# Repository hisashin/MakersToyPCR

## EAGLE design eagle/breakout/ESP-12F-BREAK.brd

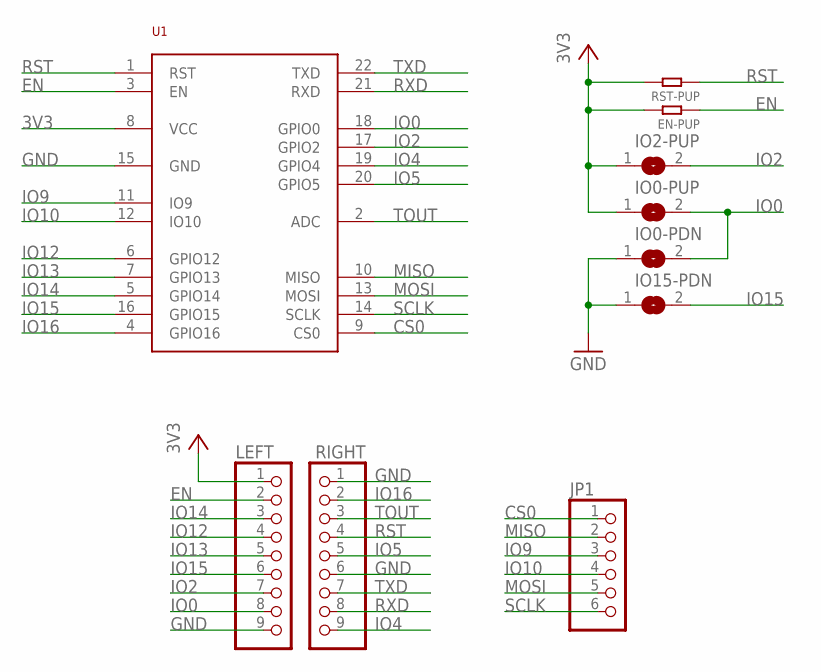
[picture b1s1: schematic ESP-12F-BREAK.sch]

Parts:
EN-PUP: 10K; R0805
IO0-PDN, IO0-PUP, IO2-PUP, IO15-PDN: SJ
JP1: PINHD-1X6; 1X06
LEFT: PINHD-1X9; 1X09
RIGHT: PINHD-1X9; 1X09
RST-PUP: 10K; R0805
U1: ESP-12F

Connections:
3V3: EN-PUP.2, IO0-PUP.1, IO2-PUP.1, LEFT.1, RST-PUP.2, U1.8 (VCC)
CS0: JP1.1, U1.9 (CS0)
EN: EN-PUP.1, LEFT.2, U1.3 (EN)
GND: IO0-PDN.1, IO15-PDN.1, LEFT.9, RIGHT.1, RIGHT.6, U1.15 (GND)
IO0: IO0-PDN.2, IO0-PUP.2, LEFT.8, U1.18 (GPIO0)
IO2: IO2-PUP.2, LEFT.7, U1.17 (GPIO2)
IO4: RIGHT.9, U1.19 (GPIO4)
IO5: RIGHT.5, U1.20 (GPIO5)
IO9: JP1.3, U1.11 (IO9)
IO10: JP1.4, U1.12 (IO10)
IO12: LEFT.4, U1.6 (GPIO12)
IO13: LEFT.5, U1.7 (GPIO13)
IO14: LEFT.3, U1.5 (GPIO14)
IO15: IO15-PDN.2, LEFT.6, U1.16 (GPIO15)
IO16: RIGHT.2, U1.4 (GPIO16)
MISO: JP1.2, U1.10 (MISO)
MOSI: JP1.5, U1.13 (MOSI)
RST: RIGHT.4, RST-PUP.1, U1.1 (RST)
RXD: RIGHT.8, U1.21 (RXD)
SCLK: JP1.6, U1.14 (SCLK)
TOUT: RIGHT.3, U1.2 (ADC)
TXD: RIGHT.7, U1.22 (TXD)

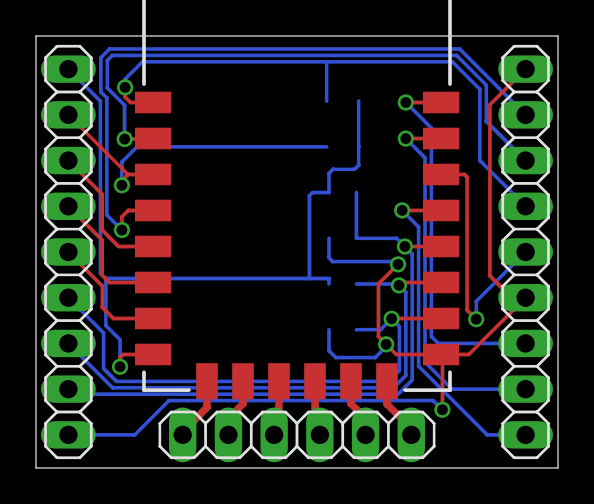
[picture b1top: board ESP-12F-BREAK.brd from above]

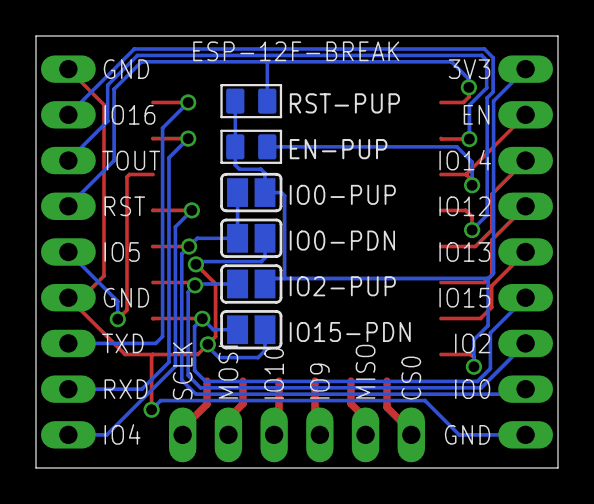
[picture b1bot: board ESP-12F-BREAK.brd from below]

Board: 2 copper layers, 29.0 x 24.0 mm, 10 parts (6 on the bottom side), 22 nets.

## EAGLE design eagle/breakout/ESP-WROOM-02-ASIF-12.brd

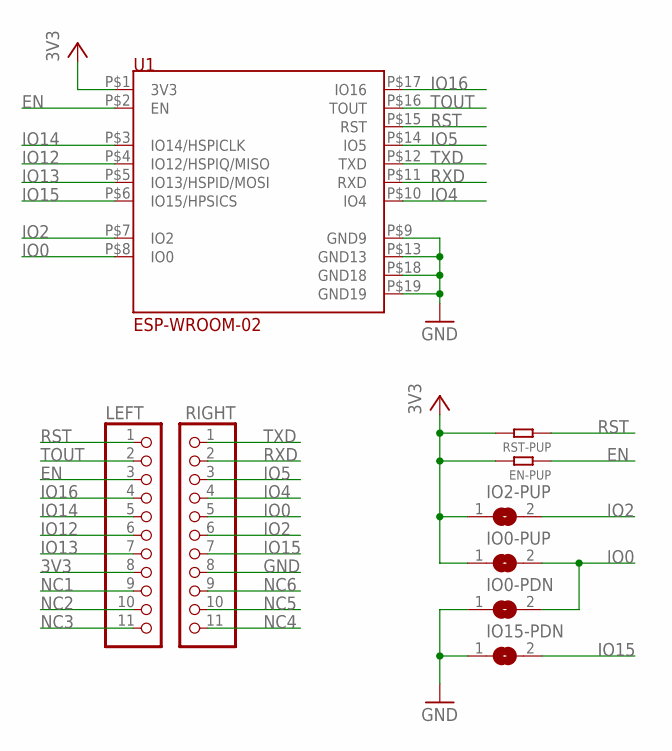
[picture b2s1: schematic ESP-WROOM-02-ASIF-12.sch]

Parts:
EN-PUP: 10K; R0805
IO0-PDN, IO0-PUP, IO2-PUP, IO15-PDN: SJ
LEFT: PINHD-1X11OCT; 1X11OCT
RIGHT: PINHD-1X11OCT; 1X11OCT
RST-PUP: 10K; R0805
U1: ESP-WROOM-02

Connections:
3V3: EN-PUP.2, IO0-PUP.1, IO2-PUP.1, LEFT.8, RST-PUP.2, U1.P$1 (3V3)
EN: EN-PUP.1, LEFT.3, U1.P$2 (EN)
GND: IO0-PDN.1, IO15-PDN.1, RIGHT.8, U1.P$9 (GND9), U1.P$13 (GND13), U1.P$18 (GND18), U1.P$19 (GND19)
IO0: IO0-PDN.2, IO0-PUP.2, RIGHT.5, U1.P$8 (IO0)
IO2: IO2-PUP.2, RIGHT.6, U1.P$7 (IO2)
IO4: RIGHT.4, U1.P$10 (IO4)
IO5: RIGHT.3, U1.P$14 (IO5)
IO12: LEFT.6, U1.P$4 (IO12/HSPIQ/MISO)
IO13: LEFT.7, U1.P$5 (IO13/HSPID/MOSI)
IO14: LEFT.5, U1.P$3 (IO14/HSPICLK)
IO15: IO15-PDN.2, RIGHT.7, U1.P$6 (IO15/HPSICS)
IO16: LEFT.4, U1.P$17 (IO16)
NC1: LEFT.9
NC2: LEFT.10
NC3: LEFT.11
NC4: RIGHT.11
NC5: RIGHT.10
NC6: RIGHT.9
RST: LEFT.1, RST-PUP.1, U1.P$15 (RST)
RXD: RIGHT.2, U1.P$11 (RXD)
TOUT: LEFT.2, U1.P$16 (TOUT)
TXD: RIGHT.1, U1.P$12 (TXD)

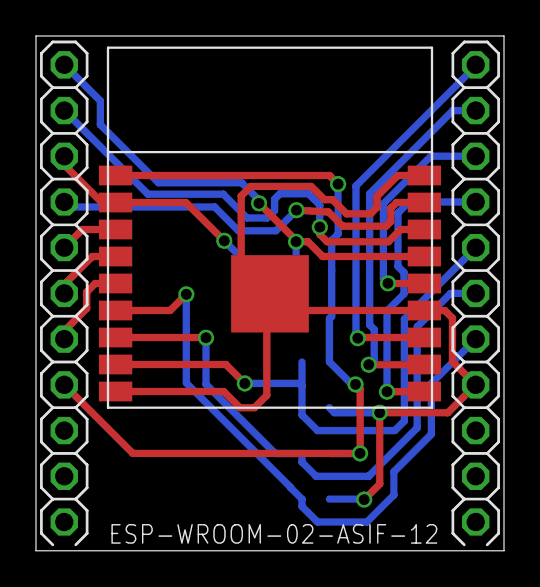
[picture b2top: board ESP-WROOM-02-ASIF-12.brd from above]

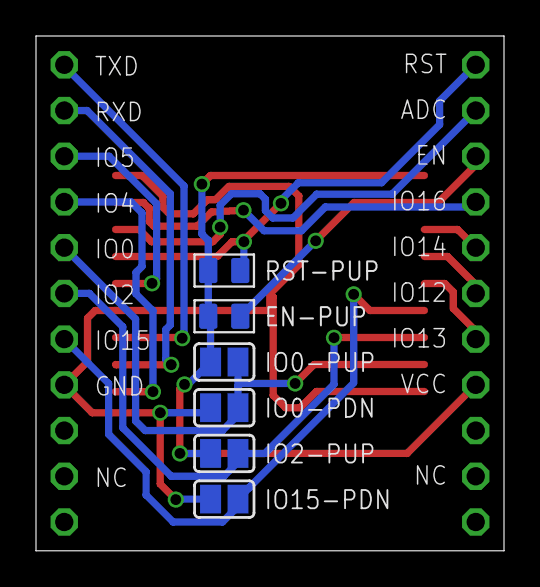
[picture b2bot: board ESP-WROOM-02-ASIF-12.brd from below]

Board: 2 copper layers, 26.0 x 28.6 mm, 9 parts (6 on the bottom side), 16 nets.

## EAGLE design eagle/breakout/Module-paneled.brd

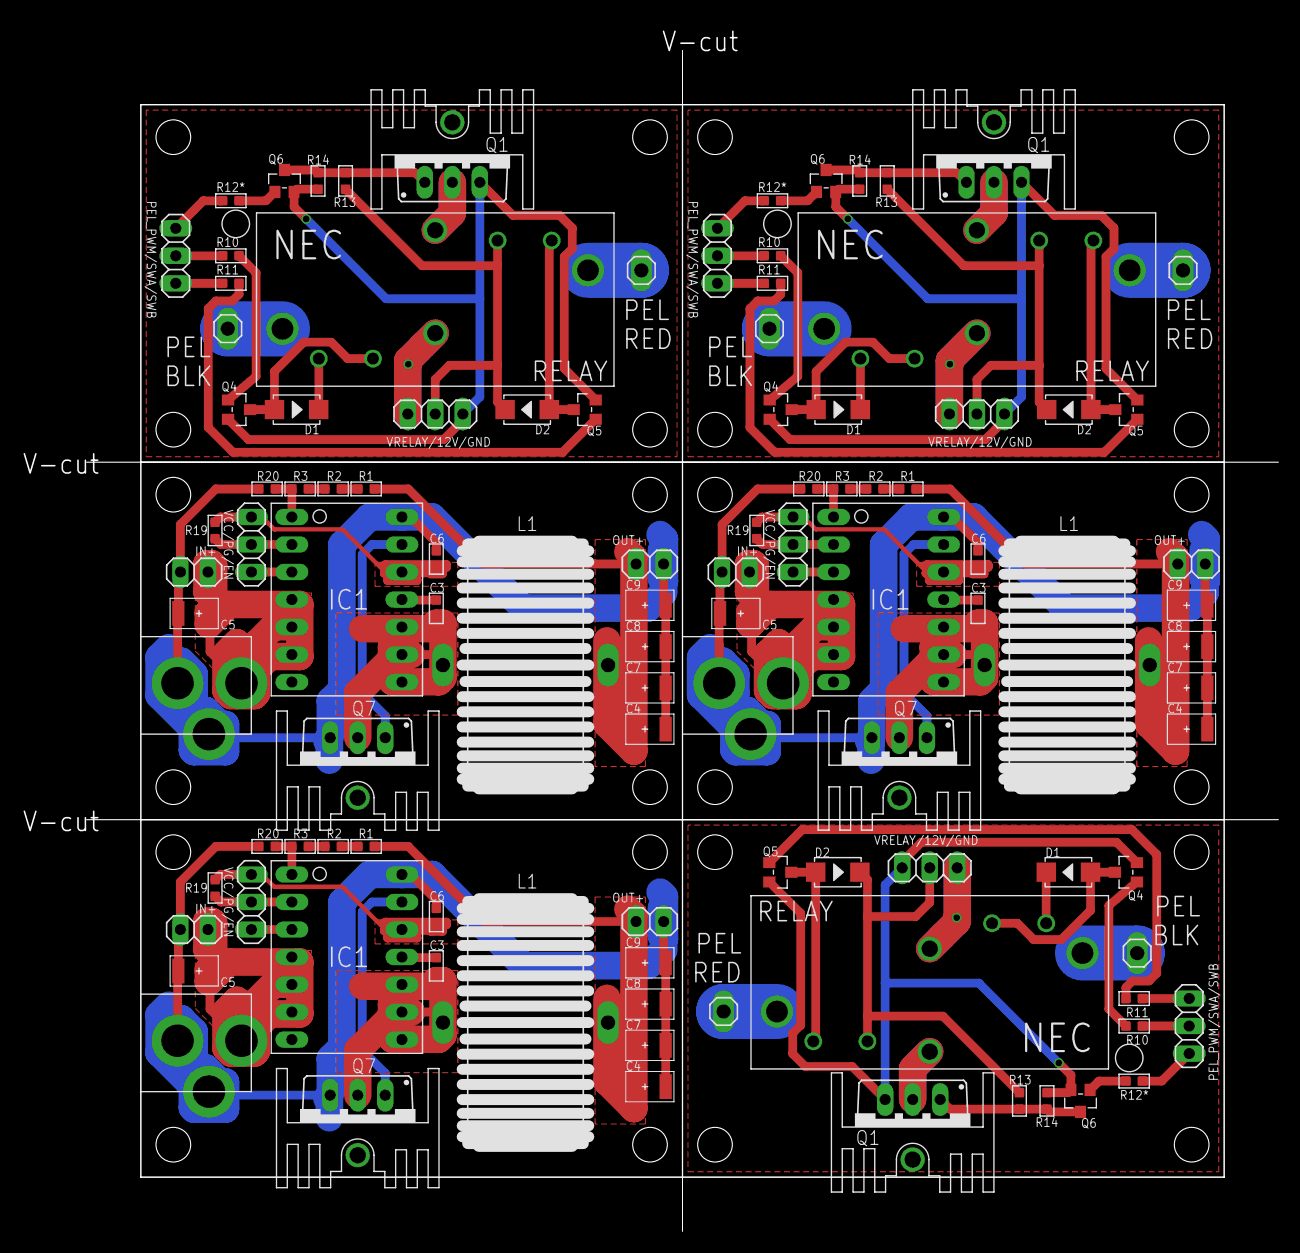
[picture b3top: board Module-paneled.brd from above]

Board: 2 copper layers, 100.0 x 99.0 mm, 111 parts (0 on the bottom side), 84 nets.

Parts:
C1, C4, C5, C7, C8, C9, C11, C12, C13, C14, C15, C18, C19, C20, C21: 22uf; AVX-B
C2, C3, C6, C10, C16, C17: 1uf; C0603
D1, D2, D3, D4, D5, D6: 1N4007; DO-214AC
HEATSINK, HEATSINK1, HEATSINK2, HEATSINK3, HEATSINK4, HEATSINK5: HEAT111PB015; HEAT11PB015
IC1, IC2, IC3: RT7258-BREAKQWB; RT7258GQW-BREAK
IN, IN1, IN2: 1X02
JACK, JACK1, JACK2: 2.1MMJACKTHM-NOOUT; PJ-102A-NOOUT
L1, L2, L3: SFT1240
LOGIC, LOGIC1, LOGIC2: 1X03
MONITOR, MONITOR1, MONITOR2: 1X03
OUT, OUT1, OUT2: 1X02
PEL_BLK, PEL_BLK1, PEL_BLK2: 1X01LONG
PEL_RED, PEL_RED1, PEL_RED2: 1X01LONG
POWER, POWER1, POWER2: 1X03
Q1, Q2, Q7, Q10, Q11, Q15: IRLB3813PBF; TO220BV
Q3, Q4, Q5, Q6, Q8, Q9, Q12, Q13, Q14: S9013; SOT-23
R1, R2, R3, R4, R5, R6, R7, R8, R10, R11, R13, R14, R15, R16, R17, R18, R19, R20, R21, R22, R23, R24, R25, R27, R28, R29, R30: 10K 1/10W; R0603
R9, R12, R26: 1K 1/10W; R0603
RELAY, RELAY1, RELAY2: NEC-RELAY2EP2; NEC-EP2

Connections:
3V1: C11.+, C12.+, C13.+, C14.+, L2.2, OUT1.1, R6.2
3V2: C18.+, C19.+, C20.+, C21.+, L3.2, OUT2.1, R23.2
3V3: C4.+, C7.+, C8.+, C9.+, L1.2, OUT.1, R1.2
12V: C5.+, IC1.P$4, IC1.P$5, IC1.P$6, IN.1, JACK.TIP
12V1: C1.+, IC2.P$4, IC2.P$5, IC2.P$6, IN1.1, JACK1.TIP
12V2: D2.2, POWER.2, R13.2, RELAY.P$6
12V3: D4.2, POWER1.2, R15.2, RELAY1.P$6
12V4: C15.+, IC3.P$4, IC3.P$5, IC3.P$6, IN2.1, JACK2.TIP
12V5: D6.2, POWER2.2, R27.2, RELAY2.P$6
EN/SYNC: IC1.P$3, MONITOR.3
EN/SYNC1: IC2.P$3, MONITOR1.3
EN/SYNC2: IC3.P$3, MONITOR2.3
FB: IC1.P$1, R3.1, R20.2
FB1: IC2.P$1, R5.2, R8.1
FB2: IC3.P$1, R22.2, R25.1
GND: C4.-, C5.-, C6.1, C7.-, C8.-, C9.-, IC1.P$14, IN.2, JACK.RING, JACK.RING_SW, OUT.2, Q7.S, R20.1
GND1: C1.-, C2.1, C11.-, C12.-, C13.-, C14.-, IC2.P$14, IN1.2, JACK1.RING, JACK1.RING_SW, OUT1.2, Q1.S, R5.1
GND2: POWER.3, Q2.S, Q4.2, Q5.2, Q6.2, R14.1
GND3: POWER1.3, Q3.2, Q8.2, Q9.2, Q10.S, R16.1
GND4: C15.-, C16.1, C18.-, C19.-, C20.-, C21.-, IC3.P$14, IN2.2, JACK2.RING, JACK2.RING_SW, OUT2.2, Q11.S, R22.1
GND5: POWER2.3, Q12.2, Q13.2, Q14.2, Q15.S, R28.1
unnamed: R2.1, R3.2
unnamed: R1.1, R2.2
unnamed: C10.2, IC2.P$11
unnamed: IC2.P$13, Q1.G
unnamed: R7.1, R8.2
unnamed: R6.1, R7.2
unnamed: Q2.D, RELAY.P$5
unnamed: Q2.G, Q6.3, R13.1, R14.2
unnamed: PEL_RED.1, RELAY.P$8
unnamed: PEL_BLK.1, RELAY.P$1
unnamed: D1.2, RELAY.P$2
unnamed: Q10.D, RELAY1.P$5
unnamed: C3.2, IC1.P$11
unnamed: Q9.3, Q10.G, R15.1, R16.2
unnamed: IC1.P$13, Q7.G
unnamed: Q9.1, R9.2
unnamed: D3.1, Q3.3, RELAY1.P$3
unnamed: D4.1, Q8.3, RELAY1.P$7
unnamed: Q3.1, R17.2
unnamed: Q8.1, R18.1
unnamed: PEL_RED1.1, RELAY1.P$8
unnamed: PEL_BLK1.1, RELAY1.P$1
unnamed: D3.2, RELAY1.P$2
unnamed: C17.2, IC3.P$11
unnamed: IC3.P$13, Q11.G
unnamed: R24.1, R25.2
unnamed: R23.1, R24.2
unnamed: Q15.D, RELAY2.P$5
unnamed: Q14.3, Q15.G, R27.1, R28.2
unnamed: Q6.1, R12.2
unnamed: Q14.1, R26.2
unnamed: D5.1, Q12.3, RELAY2.P$3
unnamed: D1.1, Q4.3, RELAY.P$3
unnamed: Q4.1, R10.2
unnamed: Q5.1, R11.1
unnamed: D2.1, Q5.3, RELAY.P$7
unnamed: D6.1, Q13.3, RELAY2.P$7
unnamed: Q12.1, R29.2
unnamed: Q13.1, R30.1
unnamed: PEL_RED2.1, RELAY2.P$8
unnamed: PEL_BLK2.1, RELAY2.P$1
unnamed: D5.2, RELAY2.P$2
PEL_PWM: LOGIC.3, R12.1
PEL_PWM1: LOGIC1.3, R9.1
PEL_PWM2: LOGIC2.3, R26.1
PEL_SWA: LOGIC.2, R10.1
PEL_SWA1: LOGIC1.2, R17.1
PEL_SWA2: LOGIC2.2, R29.1
PEL_SWB: LOGIC.1, R11.2
PEL_SWB1: LOGIC1.1, R18.2
PEL_SWB2: LOGIC2.1, R30.2
PGOOD: IC1.P$2, MONITOR.2, R19.2
PGOOD1: IC2.P$2, MONITOR1.2, R4.2
PGOOD2: IC3.P$2, MONITOR2.2, R21.2
SW: C3.1, IC1.P$8, IC1.P$9, IC1.P$10, L1.1, Q7.D
SW1: C10.1, IC2.P$8, IC2.P$9, IC2.P$10, L2.1, Q1.D
SW2: C17.1, IC3.P$8, IC3.P$9, IC3.P$10, L3.1, Q11.D
VCC: C6.2, IC1.P$12, MONITOR.1, R19.1
VCC1: C2.2, IC2.P$12, MONITOR1.1, R4.1
VCC2: C16.2, IC3.P$12, MONITOR2.1, R21.1
VRELAY: POWER.1, RELAY.P$4
VRELAY1: POWER1.1, RELAY1.P$4
VRELAY2: POWER2.1, RELAY2.P$4

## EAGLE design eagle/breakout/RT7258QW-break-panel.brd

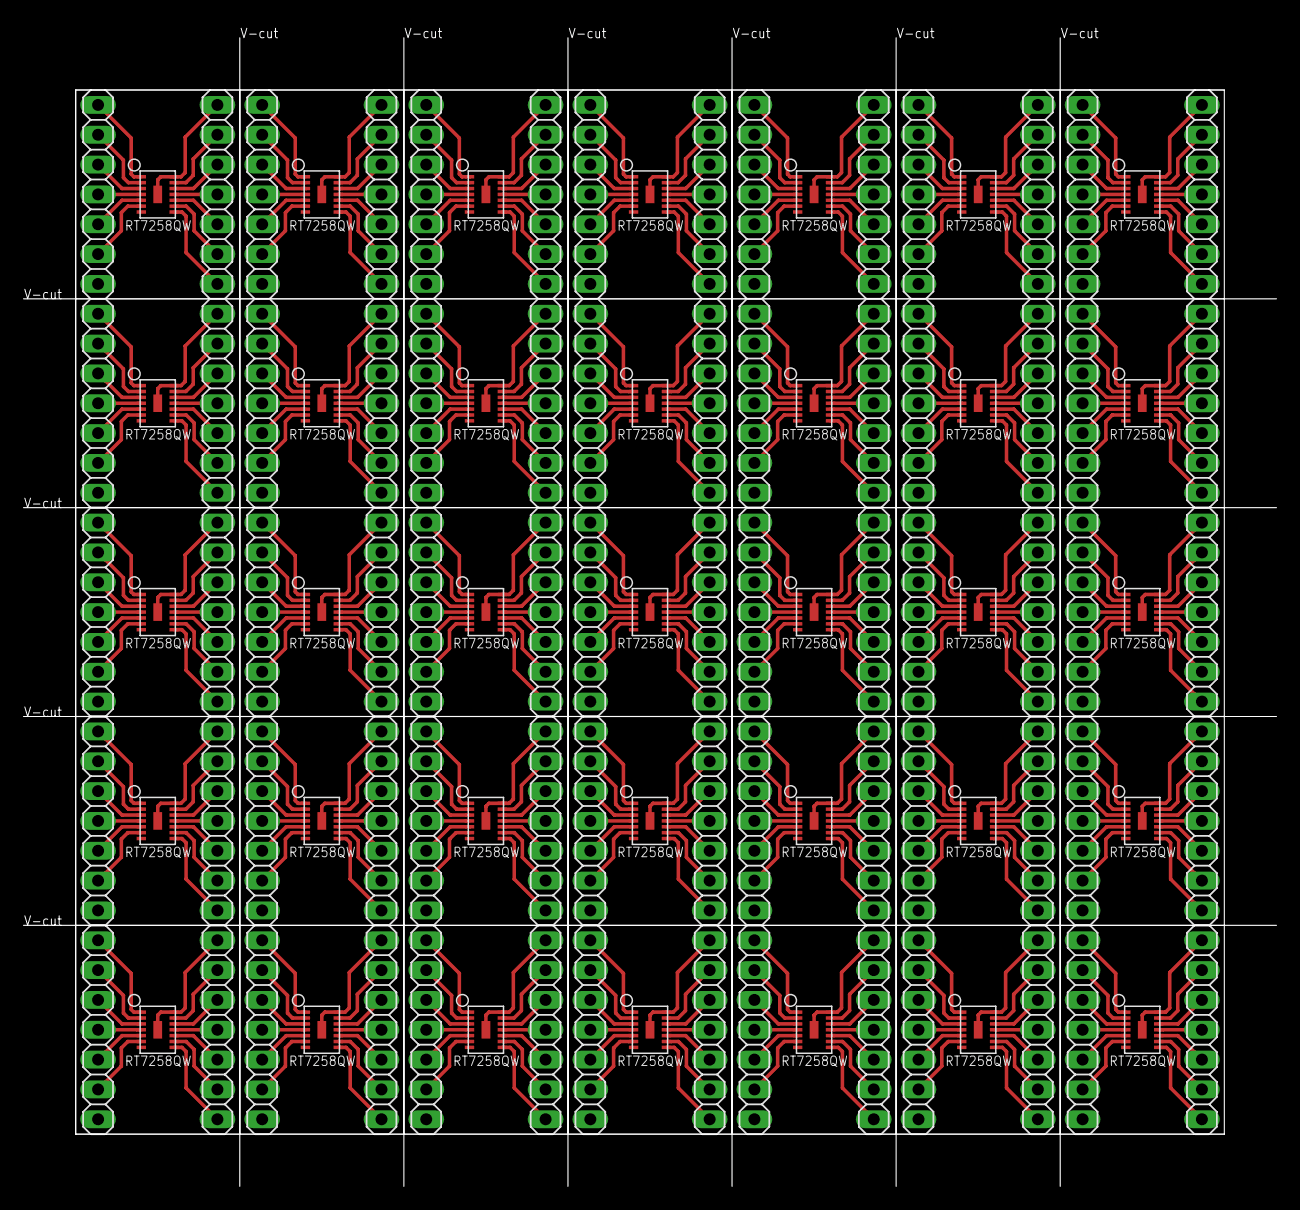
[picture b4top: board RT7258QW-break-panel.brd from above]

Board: 2 copper layers, 106.7 x 97.8 mm, 105 parts (0 on the bottom side), 455 nets.

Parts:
JP1, JP2, JP3, JP4, JP5, JP6, JP7, JP8, JP9, JP10, JP11, JP12, JP13, JP14, JP15, JP16, JP17, JP18, JP19, JP20, JP21, JP22, JP23, JP24, JP25, JP26, JP27, JP28, JP29, JP30, JP31, JP32, JP33, JP34, JP35, JP36, JP37, JP38, JP39, JP40, JP41, JP42, JP43, JP44, JP45, JP46, JP47, JP48, JP49, JP50, JP51, JP52, JP53, JP54, JP55, JP56, JP57, JP58, JP59, JP60, JP61, JP62, JP63, JP64, JP65, JP66, JP67, JP68, JP69, JP70: 1X07
U$1, U$2, U$3, U$4, U$5, U$6, U$7, U$8, U$9, U$10, U$11, U$12, U$13, U$14, U$15, U$16, U$17, U$18, U$19, U$20, U$21, U$22, U$23, U$24, U$25, U$26, U$27, U$28, U$29, U$30, U$31, U$32, U$33, U$34, U$35: RT7258QW; RT7258GQW

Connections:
1: JP1.1, U$1.P$1
2: JP1.2, U$1.P$2
3: JP1.3, U$1.P$3
4: JP1.4, U$1.P$4
5: JP1.5, U$1.P$5
6: JP1.6, U$1.P$6
8: JP2.7, U$1.P$8
9: JP2.6, U$1.P$9
10: JP2.5, U$1.P$10
11: JP2.4, U$1.P$11
12: JP2.3, U$1.P$12
13: JP2.2, U$1.P$13
14: JP2.1, U$1.P$14, U$1.P$15
16: JP3.4, U$2.P$4
17: JP3.5, U$2.P$5
18: JP3.6, U$2.P$6
19: JP4.3, U$2.P$12
20: JP3.2, U$2.P$2
21: JP3.3, U$2.P$3
22: JP4.1, U$2.P$14, U$2.P$15
23: JP3.1, U$2.P$1
24: JP4.2, U$2.P$13
25: JP4.5, U$2.P$10
26: JP4.6, U$2.P$9
27: JP4.7, U$2.P$8
28: JP4.4, U$2.P$11
30: JP5.4, U$3.P$4
31: JP5.5, U$3.P$5
32: JP5.6, U$3.P$6
33: JP6.3, U$3.P$12
34: JP5.2, U$3.P$2
35: JP5.3, U$3.P$3
36: JP6.1, U$3.P$14, U$3.P$15
37: JP5.1, U$3.P$1
38: JP6.2, U$3.P$13
39: JP6.5, U$3.P$10
40: JP6.6, U$3.P$9
41: JP6.7, U$3.P$8
42: JP6.4, U$3.P$11
44: JP7.4, U$4.P$4
45: JP7.5, U$4.P$5
46: JP7.6, U$4.P$6
47: JP8.3, U$4.P$12
48: JP7.2, U$4.P$2
49: JP7.3, U$4.P$3
50: JP8.1, U$4.P$14, U$4.P$15
51: JP7.1, U$4.P$1
52: JP8.2, U$4.P$13
53: JP8.5, U$4.P$10
54: JP8.6, U$4.P$9
55: JP8.7, U$4.P$8
56: JP8.4, U$4.P$11
58: JP9.4, U$5.P$4
59: JP9.5, U$5.P$5
60: JP9.6, U$5.P$6
61: JP10.3, U$5.P$12
62: JP9.2, U$5.P$2
63: JP9.3, U$5.P$3
64: JP10.1, U$5.P$14, U$5.P$15
65: JP9.1, U$5.P$1
66: JP10.2, U$5.P$13
67: JP10.5, U$5.P$10
68: JP10.6, U$5.P$9
69: JP10.7, U$5.P$8
70: JP10.4, U$5.P$11
72: JP11.4, U$6.P$4
73: JP11.5, U$6.P$5
74: JP11.6, U$6.P$6
75: JP12.3, U$6.P$12
76: JP11.2, U$6.P$2
77: JP11.3, U$6.P$3
78: JP12.1, U$6.P$14, U$6.P$15
79: JP11.1, U$6.P$1
80: JP12.2, U$6.P$13
81: JP12.5, U$6.P$10
82: JP12.6, U$6.P$9
83: JP12.7, U$6.P$8
84: JP12.4, U$6.P$11
86: JP13.4, U$7.P$4
87: JP13.5, U$7.P$5
88: JP13.6, U$7.P$6
89: JP14.3, U$7.P$12
90: JP13.2, U$7.P$2
91: JP13.3, U$7.P$3
92: JP14.1, U$7.P$14, U$7.P$15
93: JP13.1, U$7.P$1
94: JP14.2, U$7.P$13
95: JP14.5, U$7.P$10
96: JP14.6, U$7.P$9
97: JP14.7, U$7.P$8
98: JP14.4, U$7.P$11
100: JP15.4, U$8.P$4
101: JP15.5, U$8.P$5
102: JP15.6, U$8.P$6
103: JP16.3, U$8.P$12
104: JP15.2, U$8.P$2
105: JP15.3, U$8.P$3
106: JP16.1, U$8.P$14, U$8.P$15
107: JP15.1, U$8.P$1
108: JP16.2, U$8.P$13
109: JP16.5, U$8.P$10
110: JP16.6, U$8.P$9
111: JP16.7, U$8.P$8
112: JP16.4, U$8.P$11
114: JP17.4, U$9.P$4
115: JP17.5, U$9.P$5
116: JP17.6, U$9.P$6
117: JP18.3, U$9.P$12
118: JP17.2, U$9.P$2
119: JP17.3, U$9.P$3
120: JP18.1, U$9.P$14, U$9.P$15
121: JP17.1, U$9.P$1
122: JP18.2, U$9.P$13
123: JP18.5, U$9.P$10
124: JP18.6, U$9.P$9
125: JP18.7, U$9.P$8
126: JP18.4, U$9.P$11
128: JP19.4, U$10.P$4
129: JP19.5, U$10.P$5
130: JP19.6, U$10.P$6
131: JP20.3, U$10.P$12
132: JP19.2, U$10.P$2
133: JP19.3, U$10.P$3
134: JP20.1, U$10.P$14, U$10.P$15
135: JP19.1, U$10.P$1
136: JP20.2, U$10.P$13
137: JP20.5, U$10.P$10
138: JP20.6, U$10.P$9
139: JP20.7, U$10.P$8
140: JP20.4, U$10.P$11
142: JP21.4, U$11.P$4
143: JP21.5, U$11.P$5
144: JP21.6, U$11.P$6
145: JP22.3, U$11.P$12
146: JP21.2, U$11.P$2
147: JP21.3, U$11.P$3
148: JP22.1, U$11.P$14, U$11.P$15
149: JP21.1, U$11.P$1
150: JP22.2, U$11.P$13
151: JP22.5, U$11.P$10
152: JP22.6, U$11.P$9
153: JP22.7, U$11.P$8
154: JP22.4, U$11.P$11
156: JP23.4, U$12.P$4
157: JP23.5, U$12.P$5
158: JP23.6, U$12.P$6
159: JP24.3, U$12.P$12
160: JP23.2, U$12.P$2
161: JP23.3, U$12.P$3
162: JP24.1, U$12.P$14, U$12.P$15
163: JP23.1, U$12.P$1
164: JP24.2, U$12.P$13
165: JP24.5, U$12.P$10
166: JP24.6, U$12.P$9
167: JP24.7, U$12.P$8
168: JP24.4, U$12.P$11
170: JP25.4, U$13.P$4
171: JP25.5, U$13.P$5
172: JP25.6, U$13.P$6
173: JP26.3, U$13.P$12
174: JP25.2, U$13.P$2
175: JP25.3, U$13.P$3
176: JP26.1, U$13.P$14, U$13.P$15
177: JP25.1, U$13.P$1
178: JP26.2, U$13.P$13
179: JP26.5, U$13.P$10
180: JP26.6, U$13.P$9
181: JP26.7, U$13.P$8
182: JP26.4, U$13.P$11
184: JP27.4, U$14.P$4
185: JP27.5, U$14.P$5
186: JP27.6, U$14.P$6
187: JP28.3, U$14.P$12
188: JP27.2, U$14.P$2
189: JP27.3, U$14.P$3
190: JP28.1, U$14.P$14, U$14.P$15
191: JP27.1, U$14.P$1
192: JP28.2, U$14.P$13
193: JP28.5, U$14.P$10
194: JP28.6, U$14.P$9
195: JP28.7, U$14.P$8
196: JP28.4, U$14.P$11
198: JP29.4, U$15.P$4
199: JP29.5, U$15.P$5
200: JP29.6, U$15.P$6
201: JP30.3, U$15.P$12
202: JP29.2, U$15.P$2
203: JP29.3, U$15.P$3
204: JP30.1, U$15.P$14, U$15.P$15
205: JP29.1, U$15.P$1
206: JP30.2, U$15.P$13
207: JP30.5, U$15.P$10
208: JP30.6, U$15.P$9
209: JP30.7, U$15.P$8
210: JP30.4, U$15.P$11
212: JP31.4, U$16.P$4
213: JP31.5, U$16.P$5
214: JP31.6, U$16.P$6
215: JP32.3, U$16.P$12
216: JP31.2, U$16.P$2
217: JP31.3, U$16.P$3
218: JP32.1, U$16.P$14, U$16.P$15
219: JP31.1, U$16.P$1
220: JP32.2, U$16.P$13
221: JP32.5, U$16.P$10
222: JP32.6, U$16.P$9
223: JP32.7, U$16.P$8
224: JP32.4, U$16.P$11
226: JP33.4, U$17.P$4
227: JP33.5, U$17.P$5
228: JP33.6, U$17.P$6
229: JP34.3, U$17.P$12
230: JP33.2, U$17.P$2
231: JP33.3, U$17.P$3
232: JP34.1, U$17.P$14, U$17.P$15
233: JP33.1, U$17.P$1
234: JP34.2, U$17.P$13
235: JP34.5, U$17.P$10
236: JP34.6, U$17.P$9
237: JP34.7, U$17.P$8
238: JP34.4, U$17.P$11
240: JP35.4, U$18.P$4
241: JP35.5, U$18.P$5
242: JP35.6, U$18.P$6
243: JP36.3, U$18.P$12
244: JP35.2, U$18.P$2
245: JP35.3, U$18.P$3
246: JP36.1, U$18.P$14, U$18.P$15
247: JP35.1, U$18.P$1
248: JP36.2, U$18.P$13
249: JP36.5, U$18.P$10
250: JP36.6, U$18.P$9
251: JP36.7, U$18.P$8
252: JP36.4, U$18.P$11
254: JP37.4, U$19.P$4
255: JP37.5, U$19.P$5
256: JP37.6, U$19.P$6
257: JP38.3, U$19.P$12
258: JP37.2, U$19.P$2
259: JP37.3, U$19.P$3
260: JP38.1, U$19.P$14, U$19.P$15
261: JP37.1, U$19.P$1
262: JP38.2, U$19.P$13
263: JP38.5, U$19.P$10
264: JP38.6, U$19.P$9
265: JP38.7, U$19.P$8
266: JP38.4, U$19.P$11
268: JP39.4, U$20.P$4
269: JP39.5, U$20.P$5
270: JP39.6, U$20.P$6
271: JP40.3, U$20.P$12
272: JP39.2, U$20.P$2
273: JP39.3, U$20.P$3
274: JP40.1, U$20.P$14, U$20.P$15
275: JP39.1, U$20.P$1
276: JP40.2, U$20.P$13
277: JP40.5, U$20.P$10
278: JP40.6, U$20.P$9
279: JP40.7, U$20.P$8
280: JP40.4, U$20.P$11
282: JP41.4, U$21.P$4
283: JP41.5, U$21.P$5
284: JP41.6, U$21.P$6
285: JP42.3, U$21.P$12
286: JP41.2, U$21.P$2
287: JP41.3, U$21.P$3
288: JP42.1, U$21.P$14, U$21.P$15
289: JP41.1, U$21.P$1
290: JP42.2, U$21.P$13
291: JP42.5, U$21.P$10
292: JP42.6, U$21.P$9
293: JP42.7, U$21.P$8
294: JP42.4, U$21.P$11
296: JP43.4, U$22.P$4
297: JP43.5, U$22.P$5
298: JP43.6, U$22.P$6
299: JP44.3, U$22.P$12
300: JP43.2, U$22.P$2
301: JP43.3, U$22.P$3
302: JP44.1, U$22.P$14, U$22.P$15
303: JP43.1, U$22.P$1
304: JP44.2, U$22.P$13
305: JP44.5, U$22.P$10
306: JP44.6, U$22.P$9
307: JP44.7, U$22.P$8
308: JP44.4, U$22.P$11
310: JP45.4, U$23.P$4
311: JP45.5, U$23.P$5
312: JP45.6, U$23.P$6
313: JP46.3, U$23.P$12
314: JP45.2, U$23.P$2
315: JP45.3, U$23.P$3
316: JP46.1, U$23.P$14, U$23.P$15
317: JP45.1, U$23.P$1
318: JP46.2, U$23.P$13
319: JP46.5, U$23.P$10
320: JP46.6, U$23.P$9
321: JP46.7, U$23.P$8
322: JP46.4, U$23.P$11
324: JP47.4, U$24.P$4
325: JP47.5, U$24.P$5
326: JP47.6, U$24.P$6
327: JP48.3, U$24.P$12
328: JP47.2, U$24.P$2
329: JP47.3, U$24.P$3
330: JP48.1, U$24.P$14, U$24.P$15
331: JP47.1, U$24.P$1
332: JP48.2, U$24.P$13
333: JP48.5, U$24.P$10
334: JP48.6, U$24.P$9
335: JP48.7, U$24.P$8
336: JP48.4, U$24.P$11
338: JP49.4, U$25.P$4
339: JP49.5, U$25.P$5
340: JP49.6, U$25.P$6
341: JP50.3, U$25.P$12
342: JP49.2, U$25.P$2
343: JP49.3, U$25.P$3
344: JP50.1, U$25.P$14, U$25.P$15
345: JP49.1, U$25.P$1
346: JP50.2, U$25.P$13
347: JP50.5, U$25.P$10
348: JP50.6, U$25.P$9
349: JP50.7, U$25.P$8
350: JP50.4, U$25.P$11
352: JP51.4, U$26.P$4
353: JP51.5, U$26.P$5
354: JP51.6, U$26.P$6
355: JP52.3, U$26.P$12
356: JP51.2, U$26.P$2
357: JP51.3, U$26.P$3
358: JP52.1, U$26.P$14, U$26.P$15
359: JP51.1, U$26.P$1
360: JP52.2, U$26.P$13
361: JP52.5, U$26.P$10
362: JP52.6, U$26.P$9
363: JP52.7, U$26.P$8
364: JP52.4, U$26.P$11
366: JP53.4, U$27.P$4
367: JP53.5, U$27.P$5
368: JP53.6, U$27.P$6
369: JP54.3, U$27.P$12
370: JP53.2, U$27.P$2
371: JP53.3, U$27.P$3
372: JP54.1, U$27.P$14, U$27.P$15
373: JP53.1, U$27.P$1
374: JP54.2, U$27.P$13
375: JP54.5, U$27.P$10
376: JP54.6, U$27.P$9
377: JP54.7, U$27.P$8
378: JP54.4, U$27.P$11
380: JP55.4, U$28.P$4
381: JP55.5, U$28.P$5
382: JP55.6, U$28.P$6
383: JP56.3, U$28.P$12
384: JP55.2, U$28.P$2
385: JP55.3, U$28.P$3
386: JP56.1, U$28.P$14, U$28.P$15
387: JP55.1, U$28.P$1
388: JP56.2, U$28.P$13
389: JP56.5, U$28.P$10
390: JP56.6, U$28.P$9
391: JP56.7, U$28.P$8
392: JP56.4, U$28.P$11
394: JP57.4, U$29.P$4
395: JP57.5, U$29.P$5
396: JP57.6, U$29.P$6
397: JP58.3, U$29.P$12
398: JP57.2, U$29.P$2
399: JP57.3, U$29.P$3
400: JP58.1, U$29.P$14, U$29.P$15
401: JP57.1, U$29.P$1
402: JP58.2, U$29.P$13
403: JP58.5, U$29.P$10
404: JP58.6, U$29.P$9
405: JP58.7, U$29.P$8
406: JP58.4, U$29.P$11
408: JP59.4, U$30.P$4
409: JP59.5, U$30.P$5
410: JP59.6, U$30.P$6
411: JP60.3, U$30.P$12
412: JP59.2, U$30.P$2
413: JP59.3, U$30.P$3
414: JP60.1, U$30.P$14, U$30.P$15
415: JP59.1, U$30.P$1
416: JP60.2, U$30.P$13
417: JP60.5, U$30.P$10
418: JP60.6, U$30.P$9
419: JP60.7, U$30.P$8
420: JP60.4, U$30.P$11
422: JP61.4, U$31.P$4
423: JP61.5, U$31.P$5
424: JP61.6, U$31.P$6
425: JP62.3, U$31.P$12
426: JP61.2, U$31.P$2
427: JP61.3, U$31.P$3
428: JP62.1, U$31.P$14, U$31.P$15
429: JP61.1, U$31.P$1
430: JP62.2, U$31.P$13
431: JP62.5, U$31.P$10
432: JP62.6, U$31.P$9
433: JP62.7, U$31.P$8
434: JP62.4, U$31.P$11
436: JP63.4, U$32.P$4
437: JP63.5, U$32.P$5
438: JP63.6, U$32.P$6
439: JP64.3, U$32.P$12
440: JP63.2, U$32.P$2
441: JP63.3, U$32.P$3
442: JP64.1, U$32.P$14, U$32.P$15
443: JP63.1, U$32.P$1
444: JP64.2, U$32.P$13
445: JP64.5, U$32.P$10
446: JP64.6, U$32.P$9
447: JP64.7, U$32.P$8
448: JP64.4, U$32.P$11
450: JP65.4, U$33.P$4
451: JP65.5, U$33.P$5
452: JP65.6, U$33.P$6
453: JP66.3, U$33.P$12
454: JP65.2, U$33.P$2
455: JP65.3, U$33.P$3
456: JP66.1, U$33.P$14, U$33.P$15
457: JP65.1, U$33.P$1
458: JP66.2, U$33.P$13
459: JP66.5, U$33.P$10
460: JP66.6, U$33.P$9
461: JP66.7, U$33.P$8
462: JP66.4, U$33.P$11
464: JP67.4, U$34.P$4
465: JP67.5, U$34.P$5
466: JP67.6, U$34.P$6
467: JP68.3, U$34.P$12
468: JP67.2, U$34.P$2
469: JP67.3, U$34.P$3
470: JP68.1, U$34.P$14, U$34.P$15
471: JP67.1, U$34.P$1
472: JP68.2, U$34.P$13
473: JP68.5, U$34.P$10
474: JP68.6, U$34.P$9
475: JP68.7, U$34.P$8
476: JP68.4, U$34.P$11
478: JP69.4, U$35.P$4
479: JP69.5, U$35.P$5
480: JP69.6, U$35.P$6
481: JP70.3, U$35.P$12
482: JP69.2, U$35.P$2
483: JP69.3, U$35.P$3
484: JP70.1, U$35.P$14, U$35.P$15
485: JP69.1, U$35.P$1
486: JP70.2, U$35.P$13
487: JP70.5, U$35.P$10
488: JP70.6, U$35.P$9
489: JP70.7, U$35.P$8
490: JP70.4, U$35.P$11

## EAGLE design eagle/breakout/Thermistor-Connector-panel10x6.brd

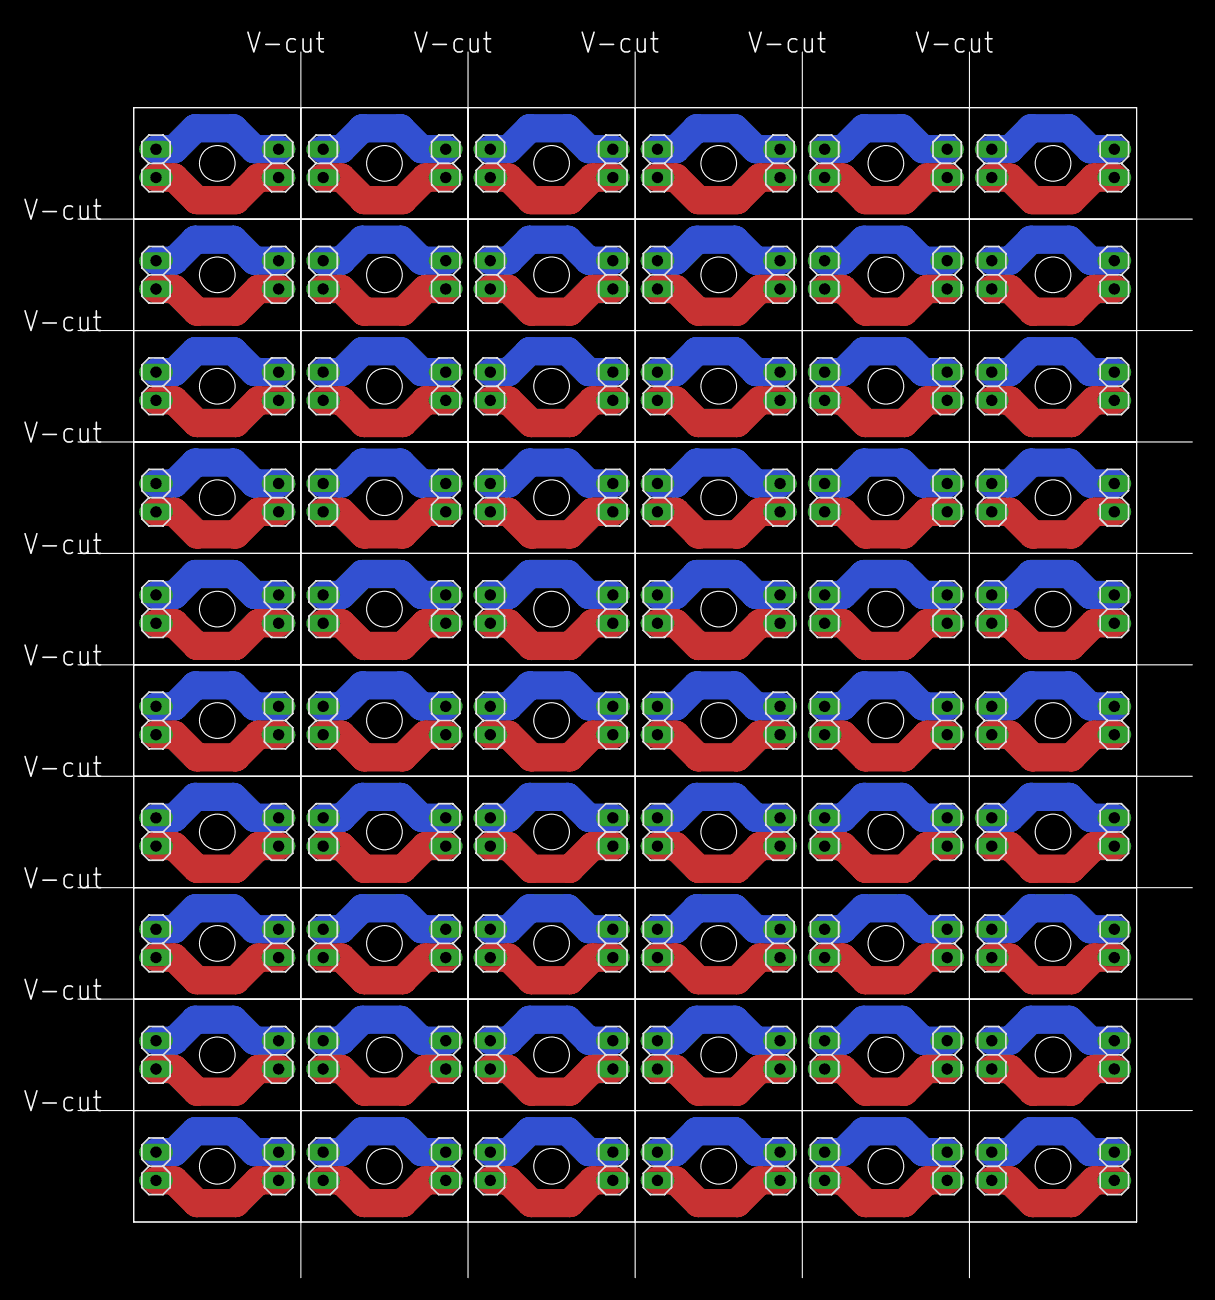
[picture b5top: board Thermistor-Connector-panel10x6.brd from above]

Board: 2 copper layers, 100.0 x 110.0 mm, 120 parts (0 on the bottom side), 120 nets.

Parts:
JP1, JP2, JP3, JP4, JP5, JP6, JP7, JP8, JP9, JP10, JP11, JP12, JP13, JP14, JP15, JP16, JP17, JP18, JP19, JP20, JP21, JP22, JP23, JP24, JP25, JP26, JP27, JP28, JP29, JP30, JP31, JP32, JP33, JP34, JP35, JP36, JP37, JP38, JP39, JP40, JP41, JP42, JP43, JP44, JP45, JP46, JP47, JP48, JP49, JP50, JP51, JP52, JP53, JP54, JP55, JP56, JP57, JP58, JP59, JP60, JP61, JP62, JP63, JP64, JP65, JP66, JP67, JP68, JP69, JP70, JP71, JP72, JP73, JP74, JP75, JP76, JP77, JP78, JP79, JP80, JP81, JP82, JP83, JP84, JP85, JP86, JP87, JP88, JP89, JP90, JP91, JP92, JP93, JP94, JP95, JP96, JP97, JP98, JP99, JP100, JP101, JP102, JP103, JP104, JP105, JP106, JP107, JP108, JP109, JP110, JP111, JP112, JP113, JP114, JP115, JP116, JP117, JP118, JP119, JP120: 1X02

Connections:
unnamed: JP1.1, JP2.1
unnamed: JP1.2, JP2.2
unnamed: JP3.1, JP4.1
unnamed: JP3.2, JP4.2
unnamed: JP5.1, JP6.1
unnamed: JP5.2, JP6.2
unnamed: JP7.1, JP8.1
unnamed: JP7.2, JP8.2
unnamed: JP9.1, JP10.1
unnamed: JP9.2, JP10.2
unnamed: JP11.1, JP12.1
unnamed: JP11.2, JP12.2
unnamed: JP13.1, JP14.1
unnamed: JP13.2, JP14.2
unnamed: JP15.1, JP16.1
unnamed: JP15.2, JP16.2
unnamed: JP17.1, JP18.1
unnamed: JP17.2, JP18.2
unnamed: JP19.1, JP20.1
unnamed: JP19.2, JP20.2
unnamed: JP21.1, JP22.1
unnamed: JP21.2, JP22.2
unnamed: JP23.1, JP24.1
unnamed: JP23.2, JP24.2
unnamed: JP25.1, JP26.1
unnamed: JP25.2, JP26.2
unnamed: JP27.1, JP28.1
unnamed: JP27.2, JP28.2
unnamed: JP29.1, JP30.1
unnamed: JP29.2, JP30.2
unnamed: JP31.1, JP32.1
unnamed: JP31.2, JP32.2
unnamed: JP33.1, JP34.1
unnamed: JP33.2, JP34.2
unnamed: JP35.1, JP36.1
unnamed: JP35.2, JP36.2
unnamed: JP37.1, JP38.1
unnamed: JP37.2, JP38.2
unnamed: JP39.1, JP40.1
unnamed: JP39.2, JP40.2
unnamed: JP41.1, JP42.1
unnamed: JP41.2, JP42.2
unnamed: JP43.1, JP44.1
unnamed: JP43.2, JP44.2
unnamed: JP45.1, JP46.1
unnamed: JP45.2, JP46.2
unnamed: JP47.1, JP48.1
unnamed: JP47.2, JP48.2
unnamed: JP49.1, JP50.1
unnamed: JP49.2, JP50.2
unnamed: JP51.1, JP52.1
unnamed: JP51.2, JP52.2
unnamed: JP53.1, JP54.1
unnamed: JP53.2, JP54.2
unnamed: JP55.1, JP56.1
unnamed: JP55.2, JP56.2
unnamed: JP57.1, JP58.1
unnamed: JP57.2, JP58.2
unnamed: JP59.1, JP60.1
unnamed: JP59.2, JP60.2
unnamed: JP61.1, JP62.1
unnamed: JP61.2, JP62.2
unnamed: JP63.1, JP64.1
unnamed: JP63.2, JP64.2
unnamed: JP65.1, JP66.1
unnamed: JP65.2, JP66.2
unnamed: JP67.1, JP68.1
unnamed: JP67.2, JP68.2
unnamed: JP69.1, JP70.1
unnamed: JP69.2, JP70.2
unnamed: JP71.1, JP72.1
unnamed: JP71.2, JP72.2
unnamed: JP73.1, JP74.1
unnamed: JP73.2, JP74.2
unnamed: JP75.1, JP76.1
unnamed: JP75.2, JP76.2
unnamed: JP77.1, JP78.1
unnamed: JP77.2, JP78.2
unnamed: JP79.1, JP80.1
unnamed: JP79.2, JP80.2
unnamed: JP81.1, JP82.1
unnamed: JP81.2, JP82.2
unnamed: JP83.1, JP84.1
unnamed: JP83.2, JP84.2
unnamed: JP85.1, JP86.1
unnamed: JP85.2, JP86.2
unnamed: JP87.1, JP88.1
unnamed: JP87.2, JP88.2
unnamed: JP89.1, JP90.1
unnamed: JP89.2, JP90.2
unnamed: JP91.1, JP92.1
unnamed: JP91.2, JP92.2
unnamed: JP93.1, JP94.1
unnamed: JP93.2, JP94.2
unnamed: JP95.1, JP96.1
unnamed: JP95.2, JP96.2
unnamed: JP97.1, JP98.1
unnamed: JP97.2, JP98.2
unnamed: JP99.1, JP100.1
unnamed: JP99.2, JP100.2
unnamed: JP101.1, JP102.1
unnamed: JP101.2, JP102.2
unnamed: JP103.1, JP104.1
unnamed: JP103.2, JP104.2
unnamed: JP105.1, JP106.1
unnamed: JP105.2, JP106.2
unnamed: JP107.1, JP108.1
unnamed: JP107.2, JP108.2
unnamed: JP109.1, JP110.1
unnamed: JP109.2, JP110.2
unnamed: JP111.1, JP112.1
unnamed: JP111.2, JP112.2
unnamed: JP113.1, JP114.1
unnamed: JP113.2, JP114.2
unnamed: JP115.1, JP116.1
unnamed: JP115.2, JP116.2
unnamed: JP117.1, JP118.1
unnamed: JP117.2, JP118.2
unnamed: JP119.1, JP120.1
unnamed: JP119.2, JP120.2
